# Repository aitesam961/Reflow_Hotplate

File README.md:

# Reflow_Hotplate

### Dear Community! 
Thanks for your interest in this project. We would like to inform you that we have noticed some bugs in the hardware part of this project. We cannot promise immediate support but we plan on fixing it as soon as we get time out of our living jobs. 
Appreciated 

A reflow Hotplate for DIY SMD assembly.

## Introduction;
This device is created as a Low-Cost solution for DIY reflow assembly of SMD components. 

## Key Features:

* Compact Design
* 9V-12V DC Input via regular DC Jack 
* 100mm x 100mm Reflow area
* High-Current protection
* PIC16F MCU to control the system
* PIC programmer Interface
* I2C LCD Support
* Detachable design [See More](https://github.com/maitesam/Reflow_Hotplate/#detachable-design)
* Temperature Probs
* UI with LCD and Pushbuttons for controlling the system.
* Low Cost & Portable

### What is Reflow Soldering?

Reflow soldering is a process in which a solder paste (a sticky mixture of powdered solder and flux) is used to temporarily attach one or thousands of tiny electrical components to their contact pads, after which the entire assembly is subjected to controlled heat. The solder paste reflows in a molten state, creating permanent solder joints. Heating may be accomplished by passing the assembly through a reflow oven.

[View more on Wikipedia](https://en.wikipedia.org/wiki/Reflow_soldering#:~:text=Reflow%20soldering%20is%20a%20process%20in%20which%20a,in%20a%20molten%20state%2C%20creating%20permanent%20solder%20joints)

### Reflow Curve
The reflow curve of the temperature of a certain point on the SMA with time when the SMA passes through the reflow oven furnace. The temperature curve provides an intuitive method to analyze the temperature change of a component during the entire reflow soldering process.
Below is the proper reflow curve a heater should achieve for perfect soldering of components.

The hOtpLaTe r0.1 manages to acheive this temperature curve by adjusting the switching duty of MOSFET which results in variation in heat.
The temperature sensor continously reads the temperatures and sends back to the Microcontroller.

### Detachable Design:
 This board is created considering all the potential issues and major use cases. The advantange is that you can use it either as a whole system by simply plugging the power in and starting the system
 OR
 You can detach the controller and Coil area of the PCB (separated by cut-lines).
 
 This makes it highly portable and Tweakers friendly.

 ### Why you may need to do this?
 The standard PCB material is FR4 which is very reliable in handling higher temperatures but it may not be very long lasting if being used very often.
 So, I came up with a backup plan and designed it in a way you can just cut the controller portion away from the coil area and use the controller with any OFF the SHELF heating element like alluminum plates.
 
 [Something Like This](https://www.aliexpress.com/item/1005003750400097.html?spm=a2g0o.productlist.0.0.39963ebdQqqQpC&algo_pvid=c2c77609-dce6-45f7-897e-77a6d6d6e77b&algo_exp_id=c2c77609-dce6-45f7-897e-77a6d6d6e77b-8&pdp_ext_f=%7B%22sku_id%22%3A%2212000027037047995%22%7D&pdp_pi=-1%3B166.96%3B-1%3B878.37%40salePrice%3BPKR%3Bsearch-mainSearch)

## Manufactruring Guidelines
You Can manufacture the PCBs from PCBWay.
[Check Out PCBWay](https://www.pcbway.com/setinvite.aspx?inviteid=440401)

Note: I am not affiliated with PCBWay. However, I just like their service and build quality.

## Assembly
It is super convenient to assemble the Hardware & Components specially if you ordered the Stencil alongwith PCBs.
After opening the Project in KiCAD, you can just scroll through the BOM and place components with respect to their designators.
OR
If you wish to order assembled PCBs, I optimized the BOM to make it super smooth and easy to source components. 
It is requested to please Open up an Issues if there is any stock outage or Manufacturing Problems.

## General Instructions
* Program the Microcontroller using CP210x/CH340x/FTDI based USB to serial converters.
* The ARDUINO IDE can be used to Program the Microcontroller.
* Power Up the Board using a PSU with 6-12V @ 2A Ratings.
*  Give Hotplate Enough time to Heatup and cooldown. Any Forced Cooldown solution is highly **NOT RECOMMENDED** as it reduces the Life of FR4 material.
* If Temperatures Higher than 270C are desired, feel free to breakdown/cutdown the Controller portion and Heating Element to avoid controller assembly meltdown. (In such case, desolder the Temperature sensor and extend it to the bottom of the hotplate using wires).

### Contributions

Contributions are what make the open source community such an amazing place to learn, inspire, and create. Any contributions you make are **greatly appreciated**.

If you have a suggestion that would make this better, please fork the repo and create a pull request. You can also simply open an issue with the tag "enhancement".
Don't forget to give the project a star! Thanks again!

1. Fork the Project
2. Create your Feature Branch (`git checkout -b feature/AmazingFeature`)
3. Commit your Changes (`git commit -m 'Add some AmazingFeature'`)
4. Push to the Branch (`git push origin feature/AmazingFeature`)
5. Open a Pull Request

## Roadmap
* [x] Proof of Concept
* [x] Research & Information
* [x] Finalizing The Idea
* [x] Schematics
* [x] PCB Design
* [x] Firmware Development
* [ ] Validation & Testing
* [x] Documentation
* [ ] Future Improvements

## Future Plans
This Hotplate is based on Regular FR4 materials that degrade over time due to excessive heating. In near future, it is desired to implement the same Idea on Alluminum Base PCBs. 
ISSUE: Alluminum would act as heatsink not letting the plate to heatup/quick cooldowns.
Community please step in.........

## License

This Project and information is published under General Public License V3.0 See `LICENSE.txt` for more information.
> https://www.gnu.org/licenses/quick-guide-gplv3.html

<p align="right">(<a href="#top">back to top</a>)</p>

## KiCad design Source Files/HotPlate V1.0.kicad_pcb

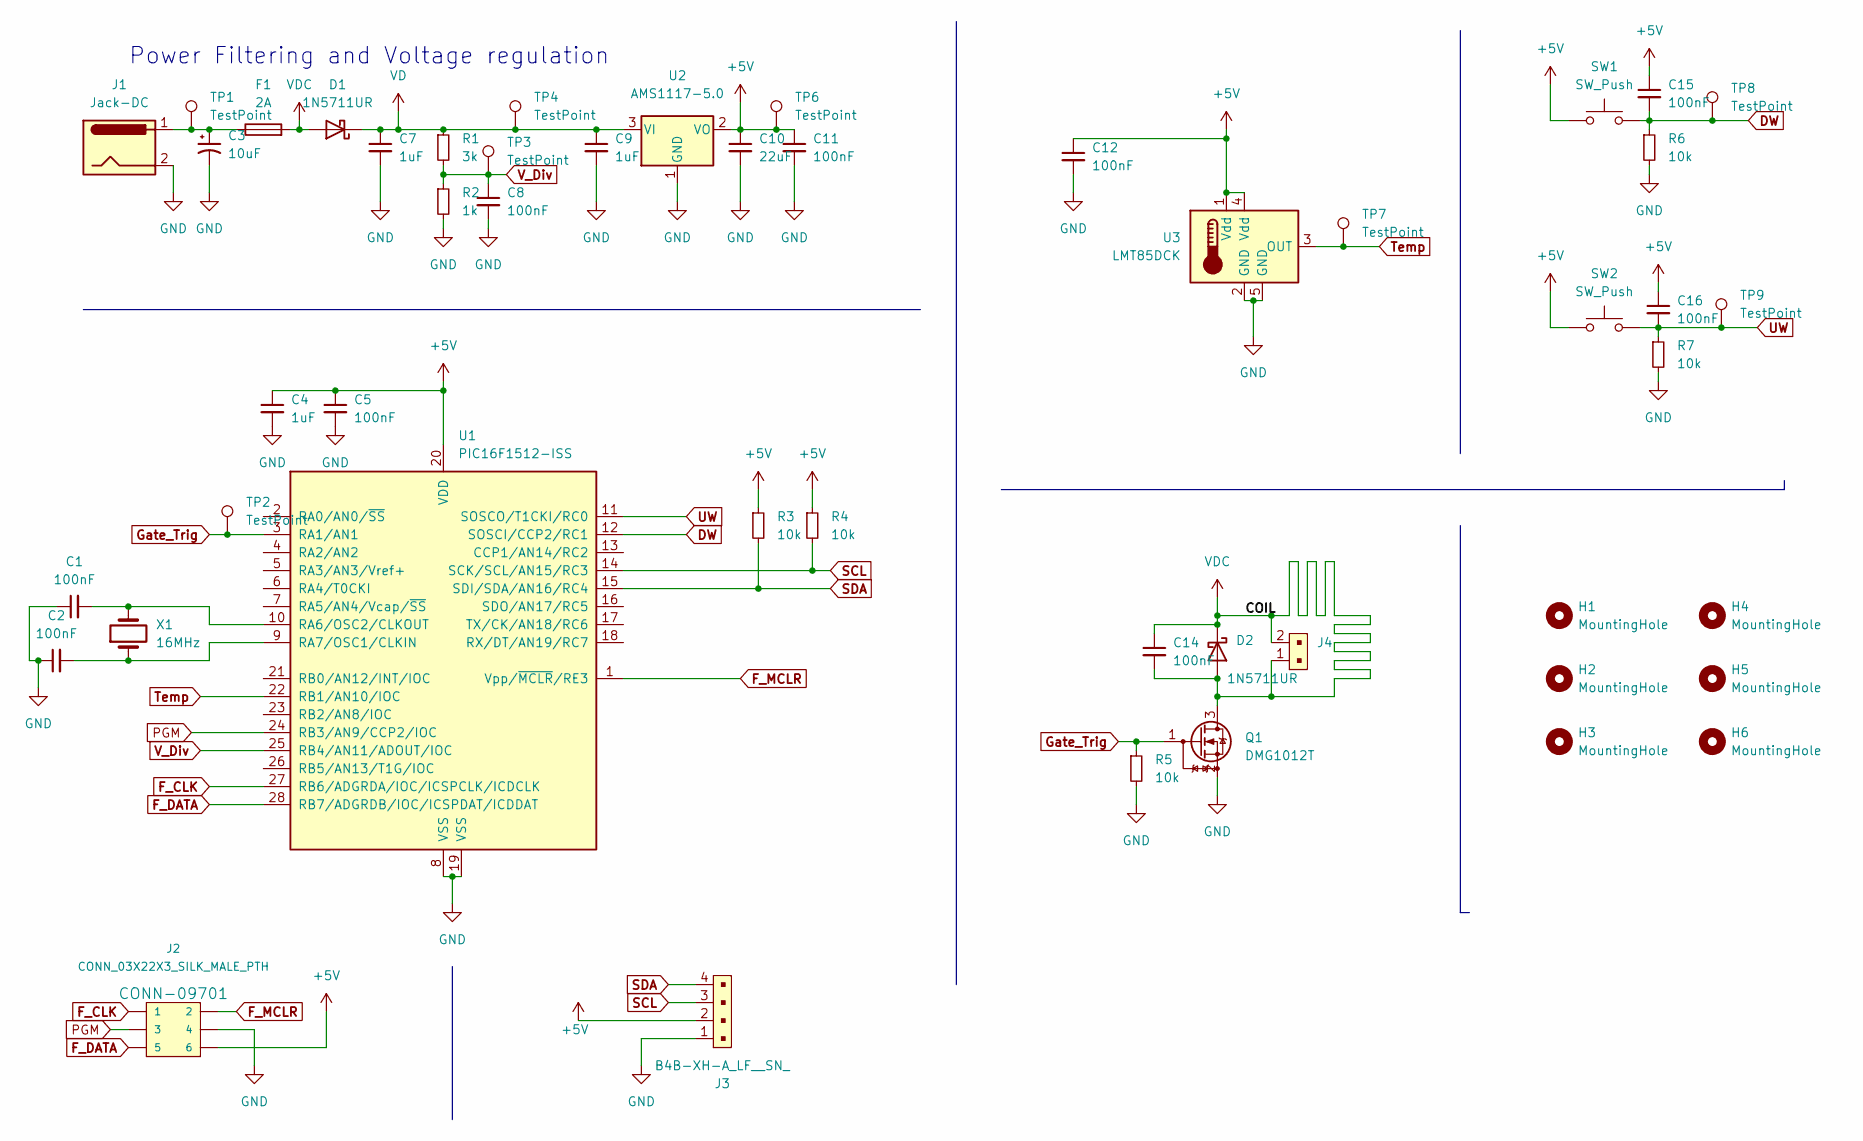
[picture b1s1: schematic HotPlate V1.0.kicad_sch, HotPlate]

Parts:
C1, C2, C5, C8, C11, C12, C14, C15, C16: 100nF; C_0603_1608Metric
C3: 10uF; CP_EIA-3528-12_Kemet-T
C4, C7, C9: 1uF; C_0603_1608Metric
C10: 22uF; CP_EIA-7260-28_AVX-M_Pad2.68x6.30mm_HandSolder
D1, D2: 1N5711UR; D_MELF
F1: 2A; Fuse_1206_3216Metric
H1, H2, H3, H4, H5, H6: MountingHole; MountingHole_3mm_Pad_Via
J1: Jack-DC; BarrelJack_CUI_PJ-102AH_Horizontal
J2: CONN_03X22X3_SILK_MALE_PTH; 2X3
J3: B4B-XH-A_LF__SN_; PinHeader_1x4_P2.5mm_Drill1.1mm; MPN B4B-XH-A(LF)(SN); Digi-Key_PN 455-2249-ND
J4: B2B-XH-A_LF__SN_; PinHeader_1x2_P2.5mm_Drill1.1mm; MPN B2B-XH-A(LF)(SN); Digi-Key_PN 455-2247-ND
Q1: DMG1012T; SOT-223
R1: 3k; R_0603_1608Metric
R2: 1k; R_0603_1608Metric
R3, R4, R5, R6, R7: 10k; R_0603_1608Metric
SW1, SW2: SW_Push; SW_PUSH_6mm
TP1, TP2, TP3, TP4, TP6, TP7, TP8, TP9: TestPoint; TestPoint_Pad_D2.0mm
U1: PIC16F1512-ISS; SSOP-28_5.3x10.2mm_P0.65mm
U2: AMS1117-5.0; SOT-223-3_TabPin2
U3: LMT85DCK; SOT-353_SC-70-5
X1: 16MHz; Crystal_SMD_HC49-SD

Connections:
+5V: C4.1, C5.1, C10.1, C11.1, C12.1, C15.1, C16.1, J2.6, J3.2, R3.1, R4.1, SW1.1, SW2.1, TP6.1, U1.20 (VDD), U2.2 (VO), U3.1 (Vdd), U3.4 (Vdd)
DW: C15.2, R6.1, SW1.2, TP8.1, U1.12 (SOSCI/CCP2/RC1)
F_CLK: J2.1, U1.27 (RB6/ADGRDA/IOC/ICSPCLK/ICDCLK)
F_DATA: J2.5, U1.28 (RB7/ADGRDB/IOC/ICSPDAT/ICDDAT)
F_MCLR: J2.2, U1.1 (Vpp/~MCLR/RE3)
GND: C1.1, C2.1, C3.2, C4.2, C5.2, C7.2, C8.2, C9.2, C10.2, C11.2, C12.2, J1.2, J1.3, J2.4, J3.1, Q1.2 (S), R2.2, R5.2, R6.2, R7.2, U1.8 (VSS), U1.19 (VSS), U2.1 (GND), U3.2 (GND), U3.5 (GND)
Gate_Trig: Q1.1 (G), R5.1, TP2.1, U1.3 (RA1/AN1)
unnamed: C1.2, U1.10 (RA6/OSC2/CLKOUT), X1.2
unnamed: C2.2, U1.9 (RA7/OSC1/CLKIN), X1.1
unnamed: C3.1, F1.1, J1.1, TP1.1
PGM: J2.3, U1.24 (RB3/AN9/CCP2/IOC)
SCL: J3.3, R4.2, U1.14 (SCK/SCL/AN15/RC3)
SDA: J3.4, R3.2, U1.15 (SDI/SDA/AN16/RC4)
Temp: TP7.1, U1.22 (RB1/AN10/IOC), U3.3 (OUT)
UW: C16.2, R7.1, SW2.2, TP9.1, U1.11 (SOSCO/T1CKI/RC0)
VD: C7.1, C9.1, D1.1 (K), R1.1, TP4.1, U2.3 (VI)
VDC: C14.1, C14.2, D1.2 (A), D2.1 (K), D2.2 (A), F1.2, J4.1, J4.2, Q1.3 (D)
V_Div: C8.1, R1.2, R2.1, TP3.1, U1.25 (RB4/AN11/ADOUT/IOC)

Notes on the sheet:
Power Filtering and Voltage regulation

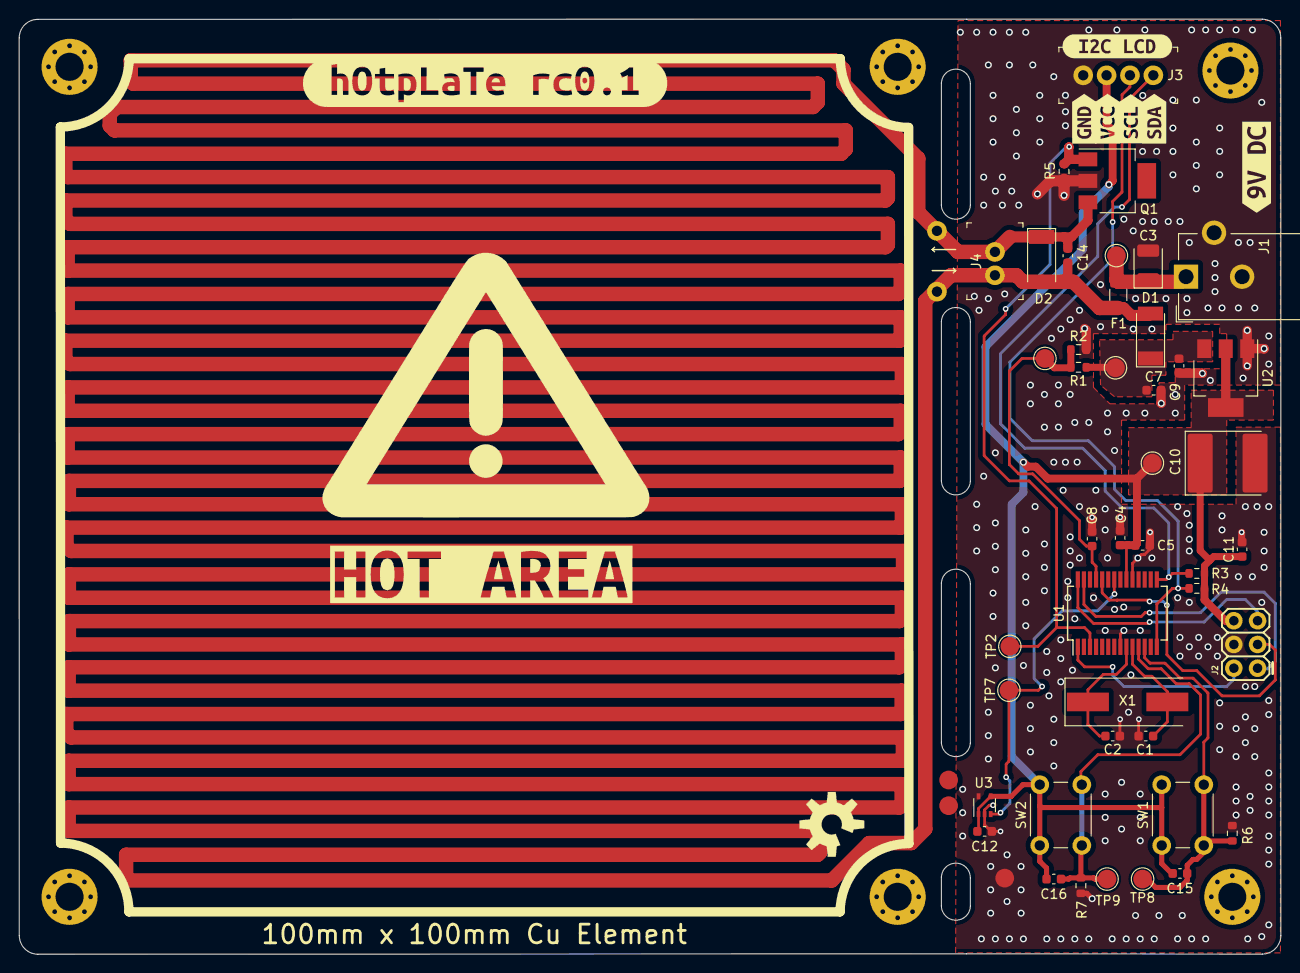
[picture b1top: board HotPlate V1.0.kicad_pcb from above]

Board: 2 copper layers, 135.0 x 100.0 mm, 57 parts (0 on the bottom side), 18 nets.

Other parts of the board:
kibuzzard-623AE740: G***; kibuzzard-623AE740
kibuzzard-623AF188: G***; kibuzzard-623AF188
kibuzzard-623B16D9: G***; kibuzzard-623B16D9
kibuzzard-623B16F0: G***; kibuzzard-623B16F0
kibuzzard-623B170E: G***; kibuzzard-623B170E
kibuzzard-623B171E: G***; kibuzzard-623B171E
kibuzzard-623B196E: G***; kibuzzard-623B196E
kibuzzard-623C18C2: G***; kibuzzard-623C18C2
